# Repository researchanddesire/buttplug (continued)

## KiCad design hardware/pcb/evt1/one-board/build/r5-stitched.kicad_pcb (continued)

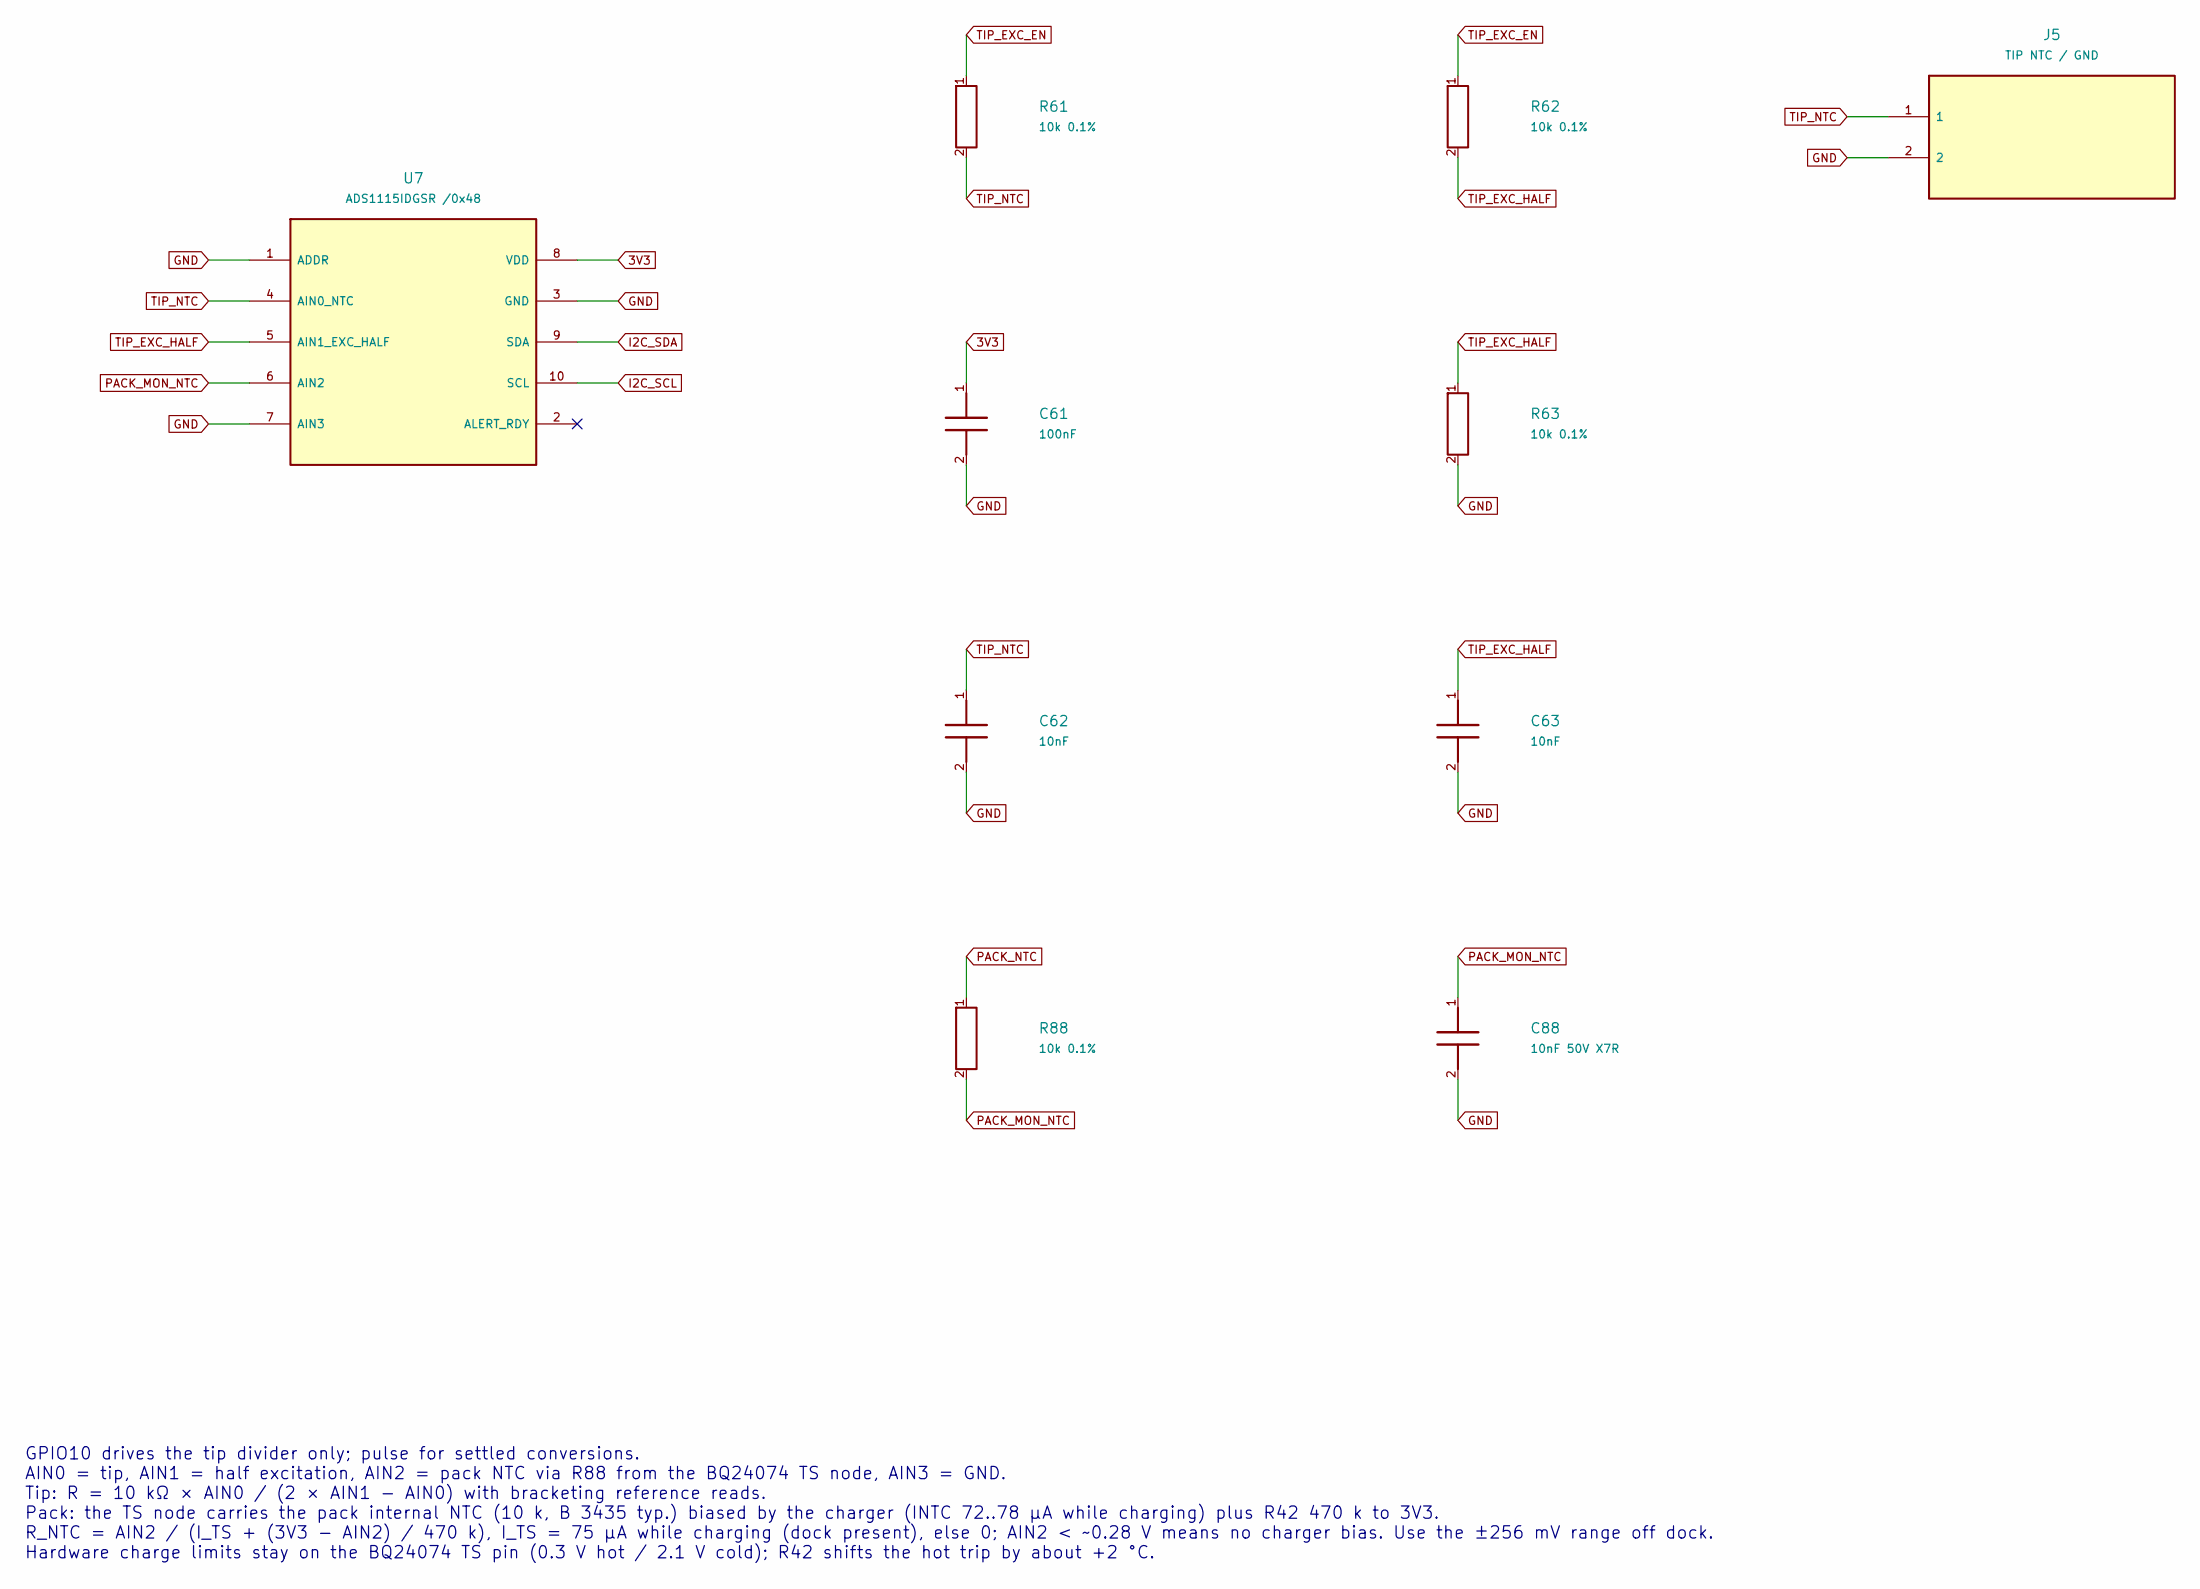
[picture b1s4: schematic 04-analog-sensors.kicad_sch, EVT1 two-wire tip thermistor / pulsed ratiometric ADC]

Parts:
C61: 100nF; C_0402_1005Metric
C62, C63: 10nF; C_0402_1005Metric
C88: 10nF 50V X7R; C_0402_1005Metric; Manufacturer Part Number GRM155R71H103KA88D
J5: TIP NTC / GND; JST_SH_SM02B-SRSS-TB_1x02-1MP_P1.00mm_Horizontal; Manufacturer Part Number SM02B-SRSS-TB(LF)(SN); LCSC Part Number C160402
R61, R62, R63: 10k 0.1%; R_0402_1005Metric
R88: 10k 0.1%; R_0402_1005Metric; Manufacturer Part Number TNPW040210K0BEED
U7: ADS1115IDGSR /0x48; VSSOP-10_3x3mm_P0.5mm

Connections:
3V3: C61.1, U7.8 (VDD); also elsewhere on the board
GND: C61.2, C62.2, C63.2, C88.2, J5.2, R63.2, U7.1 (ADDR), U7.3 (GND), U7.7 (AIN3); also elsewhere on the board
I2C_SCL: U7.10 (SCL); also elsewhere on the board
I2C_SDA: U7.9 (SDA); also elsewhere on the board
PACK_MON_NTC: C88.1, R88.2, U7.6 (AIN2); also elsewhere on the board
TIP_EXC_HALF: C63.1, R62.2, R63.1, U7.5 (AIN1_EXC_HALF)
TIP_NTC: C62.1, J5.1, R61.2, U7.4 (AIN0_NTC)

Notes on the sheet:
GPIO10 drives the tip divider only; pulse for settled conversions. AIN0 = tip, AIN1 = half excitation, AIN2 = pack NTC via R88 from the BQ24074 TS node, AIN3 = GND. Tip: R = 10 kΩ × AIN0 / (2 × AIN1 − AIN0) with bracketing reference reads. Pack: the TS node carries the pack internal NTC (10 k, B 34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

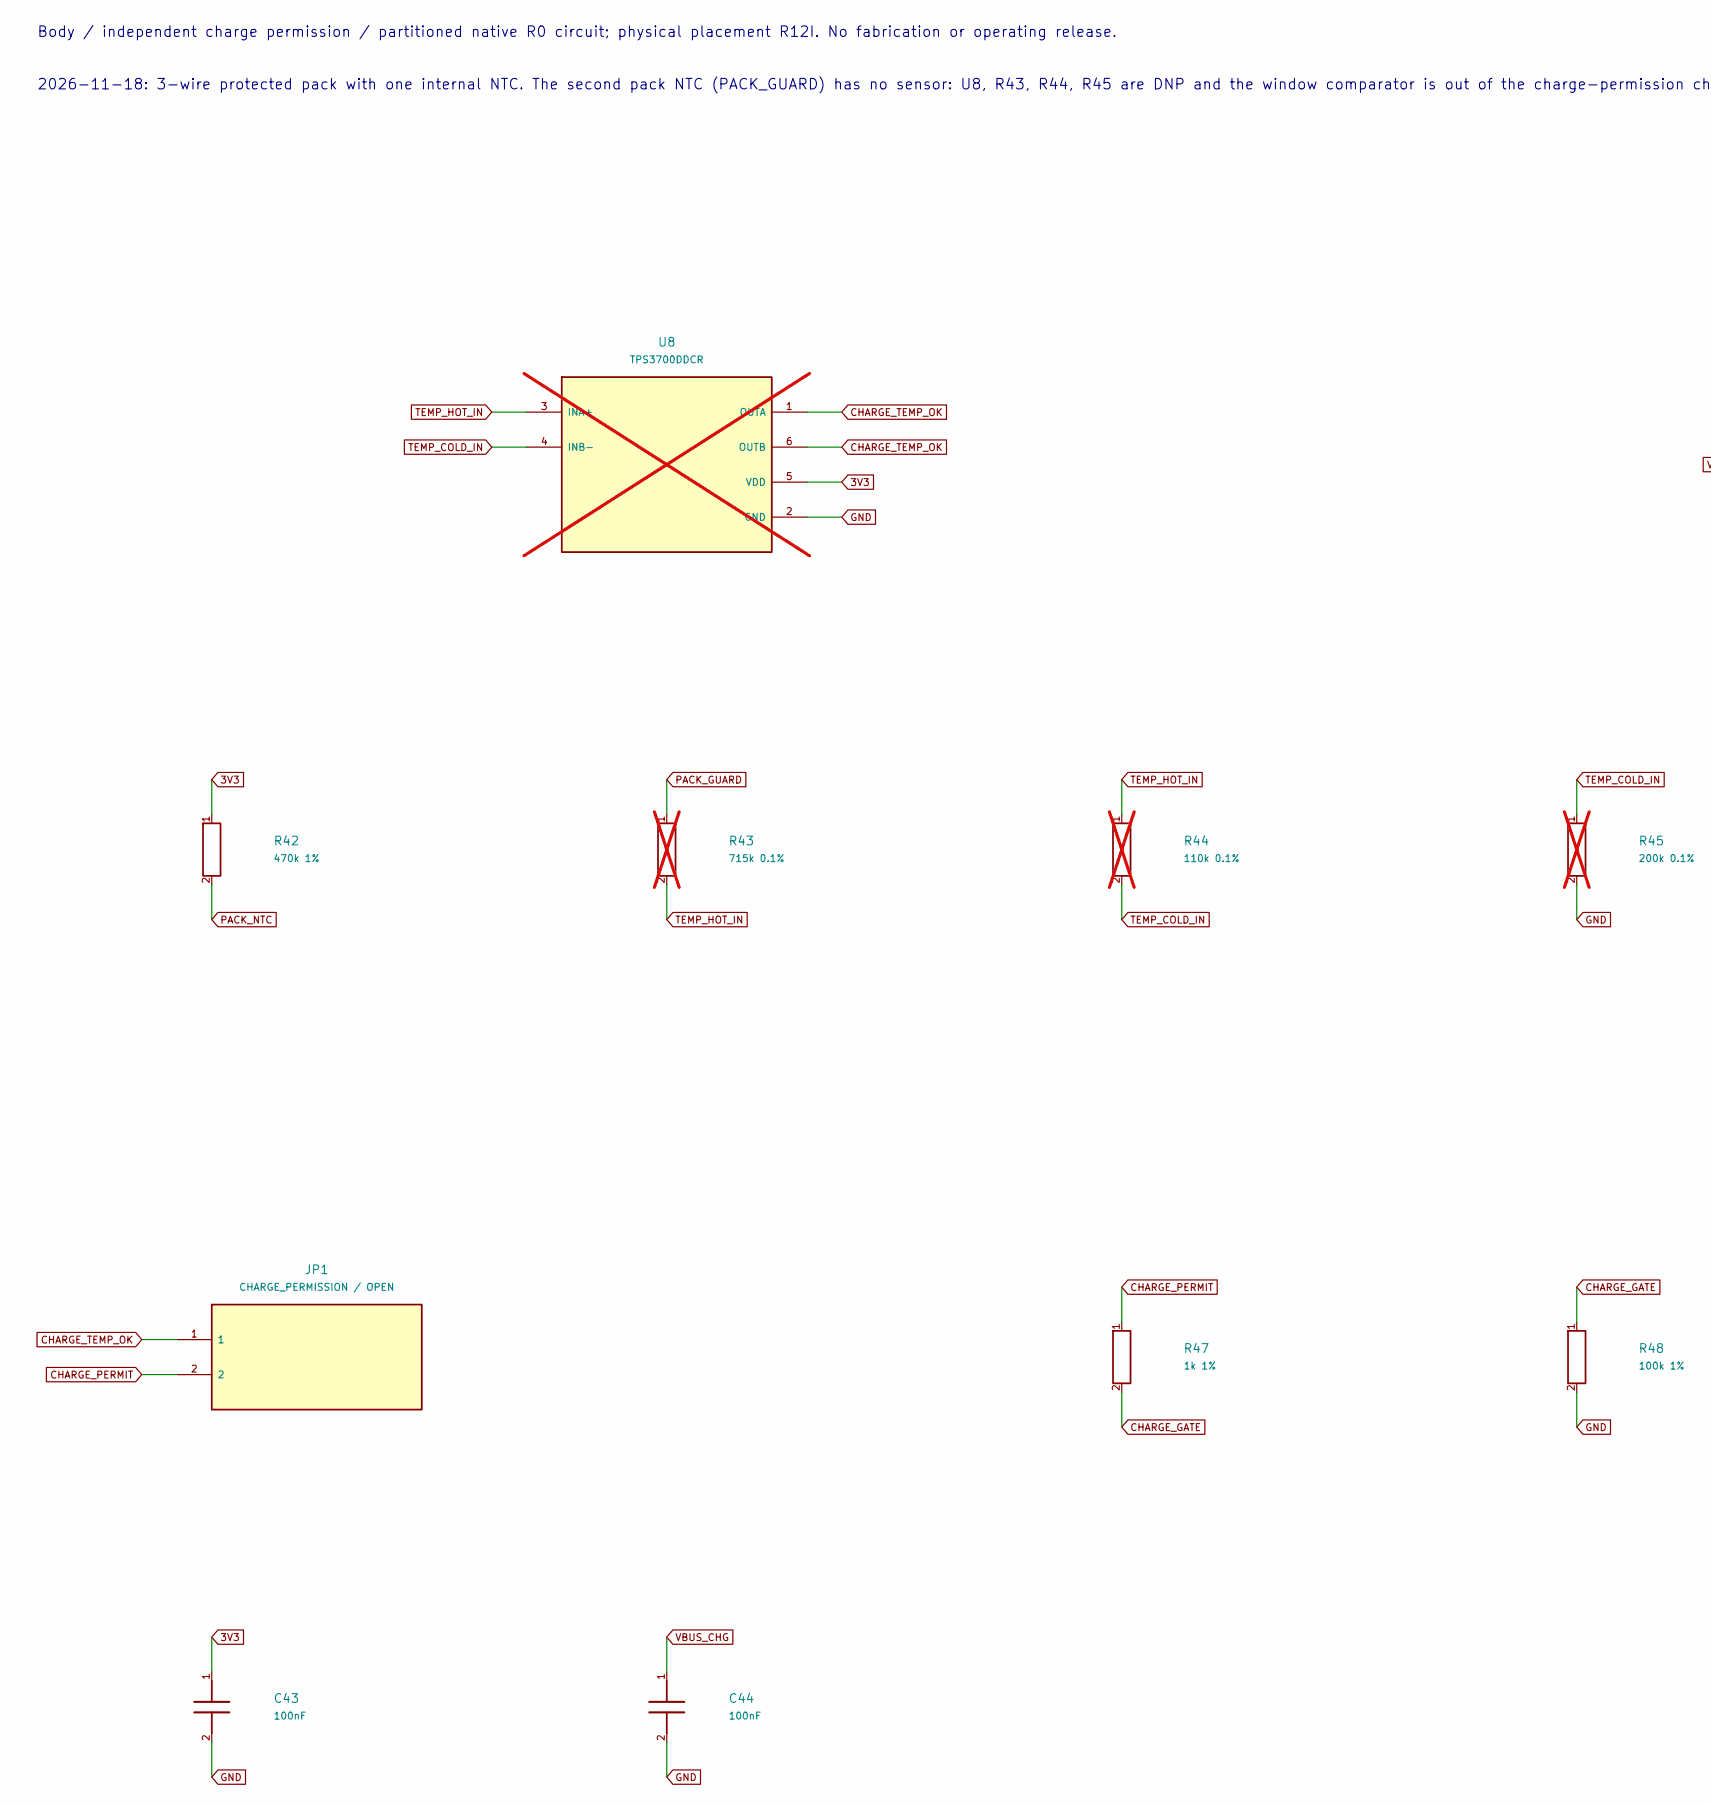
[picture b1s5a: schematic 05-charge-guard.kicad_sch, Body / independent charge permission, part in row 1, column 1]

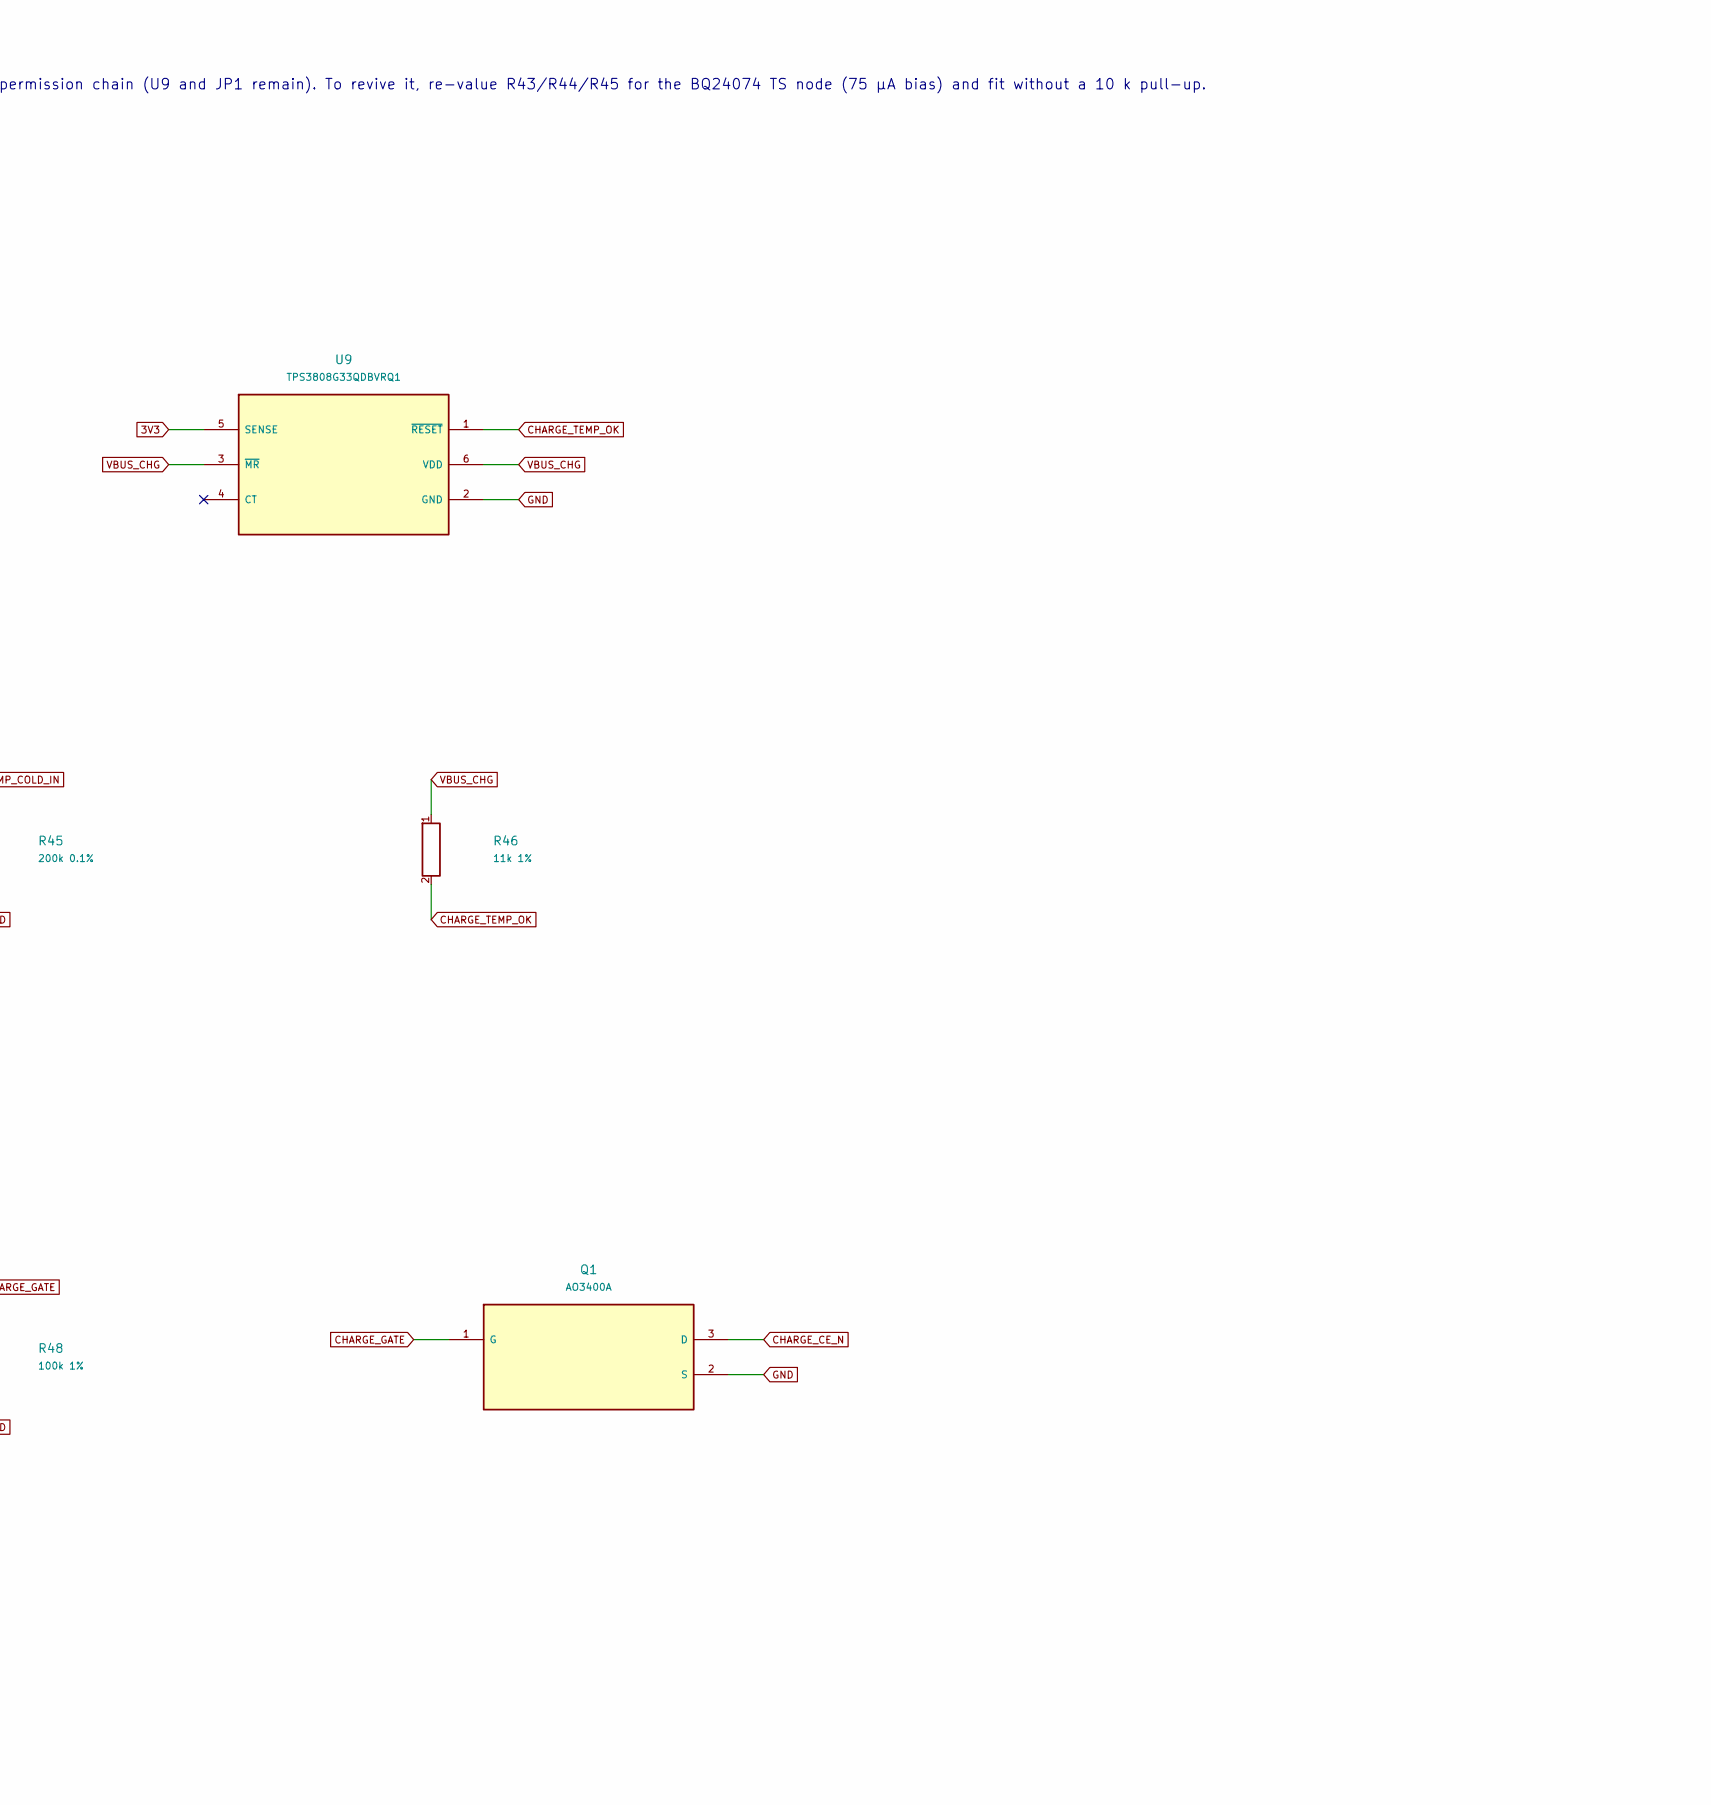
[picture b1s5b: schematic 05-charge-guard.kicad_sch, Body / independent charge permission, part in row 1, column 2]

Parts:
C43, C44: 100nF; Murata_GRM18_0603_Reflow
JP1: CHARGE_PERMISSION / OPEN; SolderJumper-2_P1.3mm_Open_RoundedPad1.0x1.5mm
Q1: AO3400A; SOT-23
R42: 470k 1%; R_0402_1005Metric; Manufacturer Part Number 0402WGF4703TCE
R43: 715k 0.1%; RESI_PTFR0805_C16003; Manufacturer Part Number PTFR0805B715KP9; LCSC Part Number C2849329; not fitted
R44: 110k 0.1%; Vishay_TNPW0603_IEC_Reflow; not fitted
R45: 200k 0.1%; Vishay_TNPW0603_IEC_Reflow; Manufacturer Part Number ERA3AEB204V; LCSC Part Number C473261; not fitted
R46: 11k 1%; R_0402_1005Metric; Manufacturer Part Number RT0402BRD0711KL; LCSC Part Number C705064
R47: 1k 1%; R_0402_1005Metric
R48: 100k 1%; R_0402_1005Metric
U8: TPS3700DDCR; TSOT-23-6; not fitted
U9: TPS3808G33QDBVRQ1; SOT-23-6; Manufacturer Part Number TPS3808G33QDBVRQ1; LCSC Part Number C414616

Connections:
3V3: C43.1, R42.1, U8.5 (VDD), U9.5 (SENSE); also elsewhere on the board
CHARGE_CE_N: Q1.3 (D); also elsewhere on the board
CHARGE_GATE: Q1.1 (G), R47.2, R48.1
CHARGE_PERMIT: JP1.2, R47.1
CHARGE_TEMP_OK: JP1.1, R46.2, U8.1 (OUTA), U8.6 (OUTB), U9.1 (~RESET)
GND: C43.2, C44.2, Q1.2 (S), R45.2, R48.2, U8.2 (GND), U9.2 (GND); also elsewhere on the board
TEMP_COLD_IN: R44.2, R45.1, U8.4 (INB-)
TEMP_HOT_IN: R43.2, R44.1, U8.3 (INA+)
VBUS_CHG: C44.1, R46.1, U9.3 (~MR), U9.6 (VDD); also elsewhere on the board

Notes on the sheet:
Body / independent charge permission / partitioned native R0 circuit; physical placement R12I. No fabrication or operating release.
2026-11-18: 3-wire protected pack with one internal NTC. The second pack NTC (PACK_GUARD) has no sensor: U8, R43, R44, R45 are DNP and the window comparator is out of the charge-permission chain (U9 and JP1 remain). To revive it, re-value R43/R44/R45 for the BQ24074 TS node (75 µA bias) and fit wit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

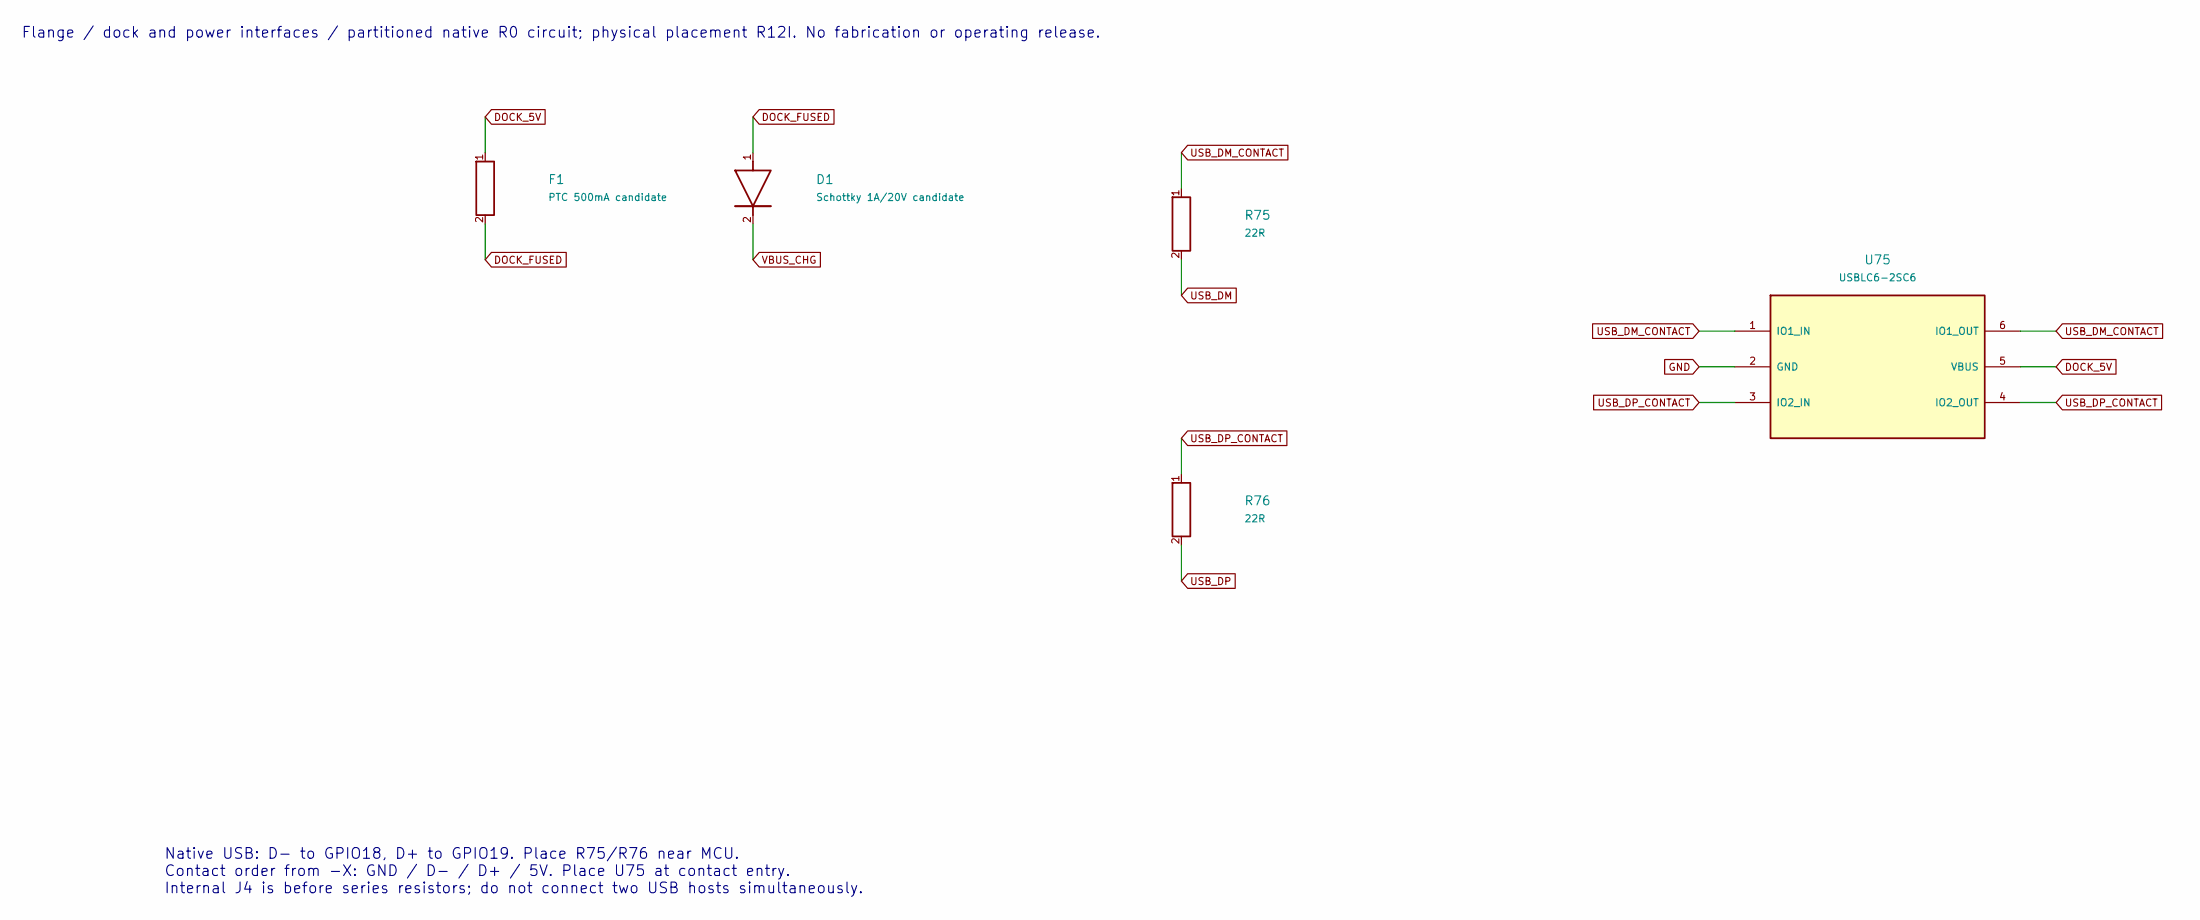
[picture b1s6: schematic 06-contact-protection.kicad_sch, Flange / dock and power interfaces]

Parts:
D1: Schottky 1A/20V candidate; Diodes_B140HW_SOD123_A1_K2
F1: PTC 500mA candidate; Fuse_1206_3216Metric
R75, R76: 22R; R_0402_1005Metric; Manufacturer Part Number RC0402FR-0722RL; LCSC Part Number C114765
U75: USBLC6-2SC6; SOT-23-6

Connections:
DOCK_5V: F1.1, U75.5 (VBUS); also elsewhere on the board
DOCK_FUSED: D1.1, F1.2
GND: U75.2 (GND); also elsewhere on the board
USB_DM: R75.2; also elsewhere on the board
USB_DM_CONTACT: R75.1, U75.1 (IO1_IN), U75.6 (IO1_OUT); also elsewhere on the board
USB_DP: R76.2; also elsewhere on the board
USB_DP_CONTACT: R76.1, U75.3 (IO2_IN), U75.4 (IO2_OUT); also elsewhere on the board
VBUS_CHG: D1.2; also elsewhere on the board

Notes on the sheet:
Flange / dock and power interfaces / partitioned native R0 circuit; physical placement R12I. No fabrication or operating release.
Native USB: D- to GPIO18, D+ to GPIO19. Place R75/R76 near MCU. Contact order from -X: GND / D- / D+ / 5V. Place U75 at contact entry. Internal J4 is before series resistors; do not connect two USB hosts simultaneously.

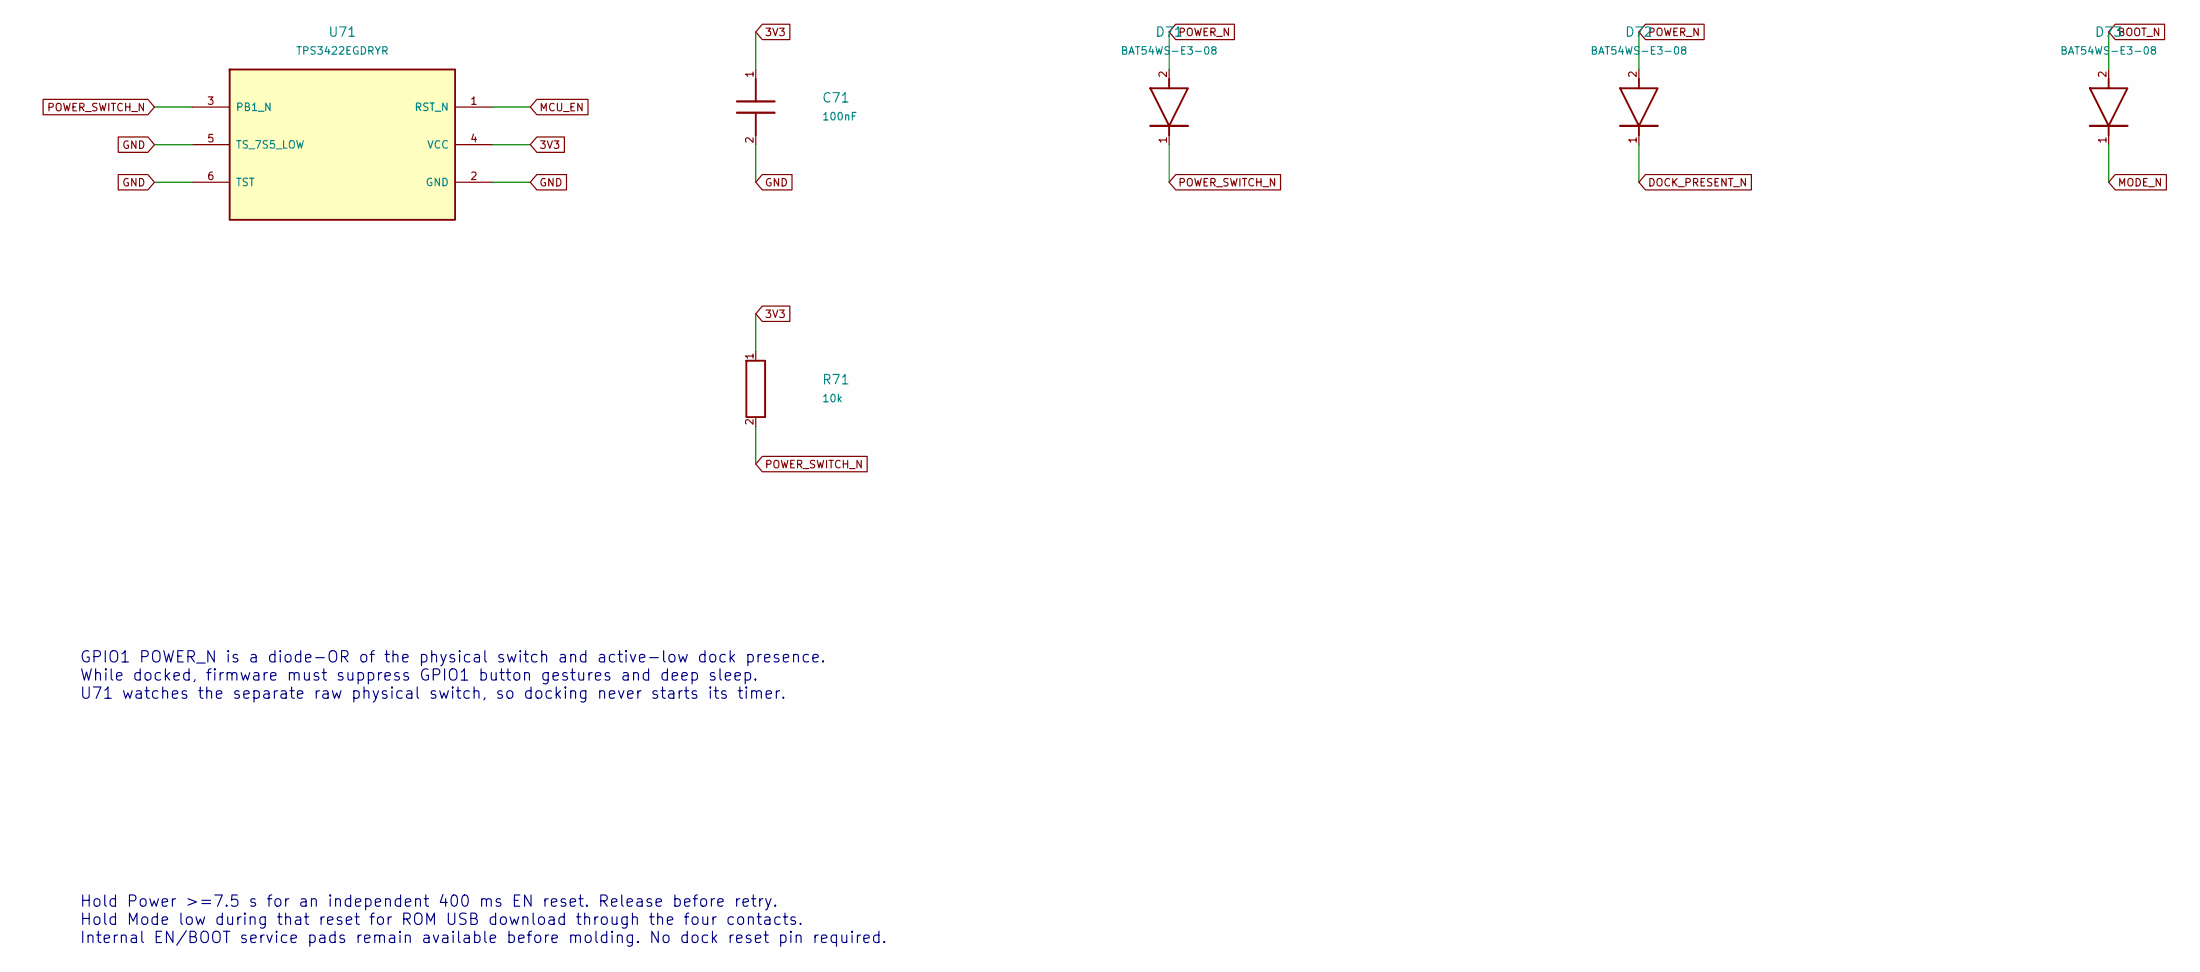
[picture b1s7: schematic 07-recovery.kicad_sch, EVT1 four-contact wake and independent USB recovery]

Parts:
C71: 100nF; C_0402_1005Metric
D71, D72, D73: BAT54WS-E3-08; D_SOD-323
R71: 10k; R_0402_1005Metric
U71: TPS3422EGDRYR; Texas_USON-6_1x1.45mm_P0.5mm_SMD

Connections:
3V3: C71.1, R71.1, U71.4 (VCC); also elsewhere on the board
BOOT_N: D73.2 (1); also elsewhere on the board
DOCK_PRESENT_N: D72.1 (2); also elsewhere on the board
GND: C71.2, U71.2 (GND), U71.5 (TS_7S5_LOW), U71.6 (TST); also elsewhere on the board
MCU_EN: U71.1 (RST_N); also elsewhere on the board
MODE_N: D73.1 (2); also elsewhere on the board
POWER_N: D71.2 (1), D72.2 (1); also elsewhere on the board
POWER_SWITCH_N: D71.1 (2), R71.2, U71.3 (PB1_N); also elsewhere on the board

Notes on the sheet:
GPIO1 POWER_N is a diode-OR of the physical switch and active-low dock presence. While docked, firmware must suppress GPIO1 button gestures and deep sleep. U71 watches the separate raw physical switch, so docking never starts its timer.
Hold Power >=7.5 s for an independent 400 ms EN reset. Release before retry. Hold Mode low during that reset for ROM USB download through the four contacts. Internal EN/BOOT service pads remain available before molding. No dock reset pin required.

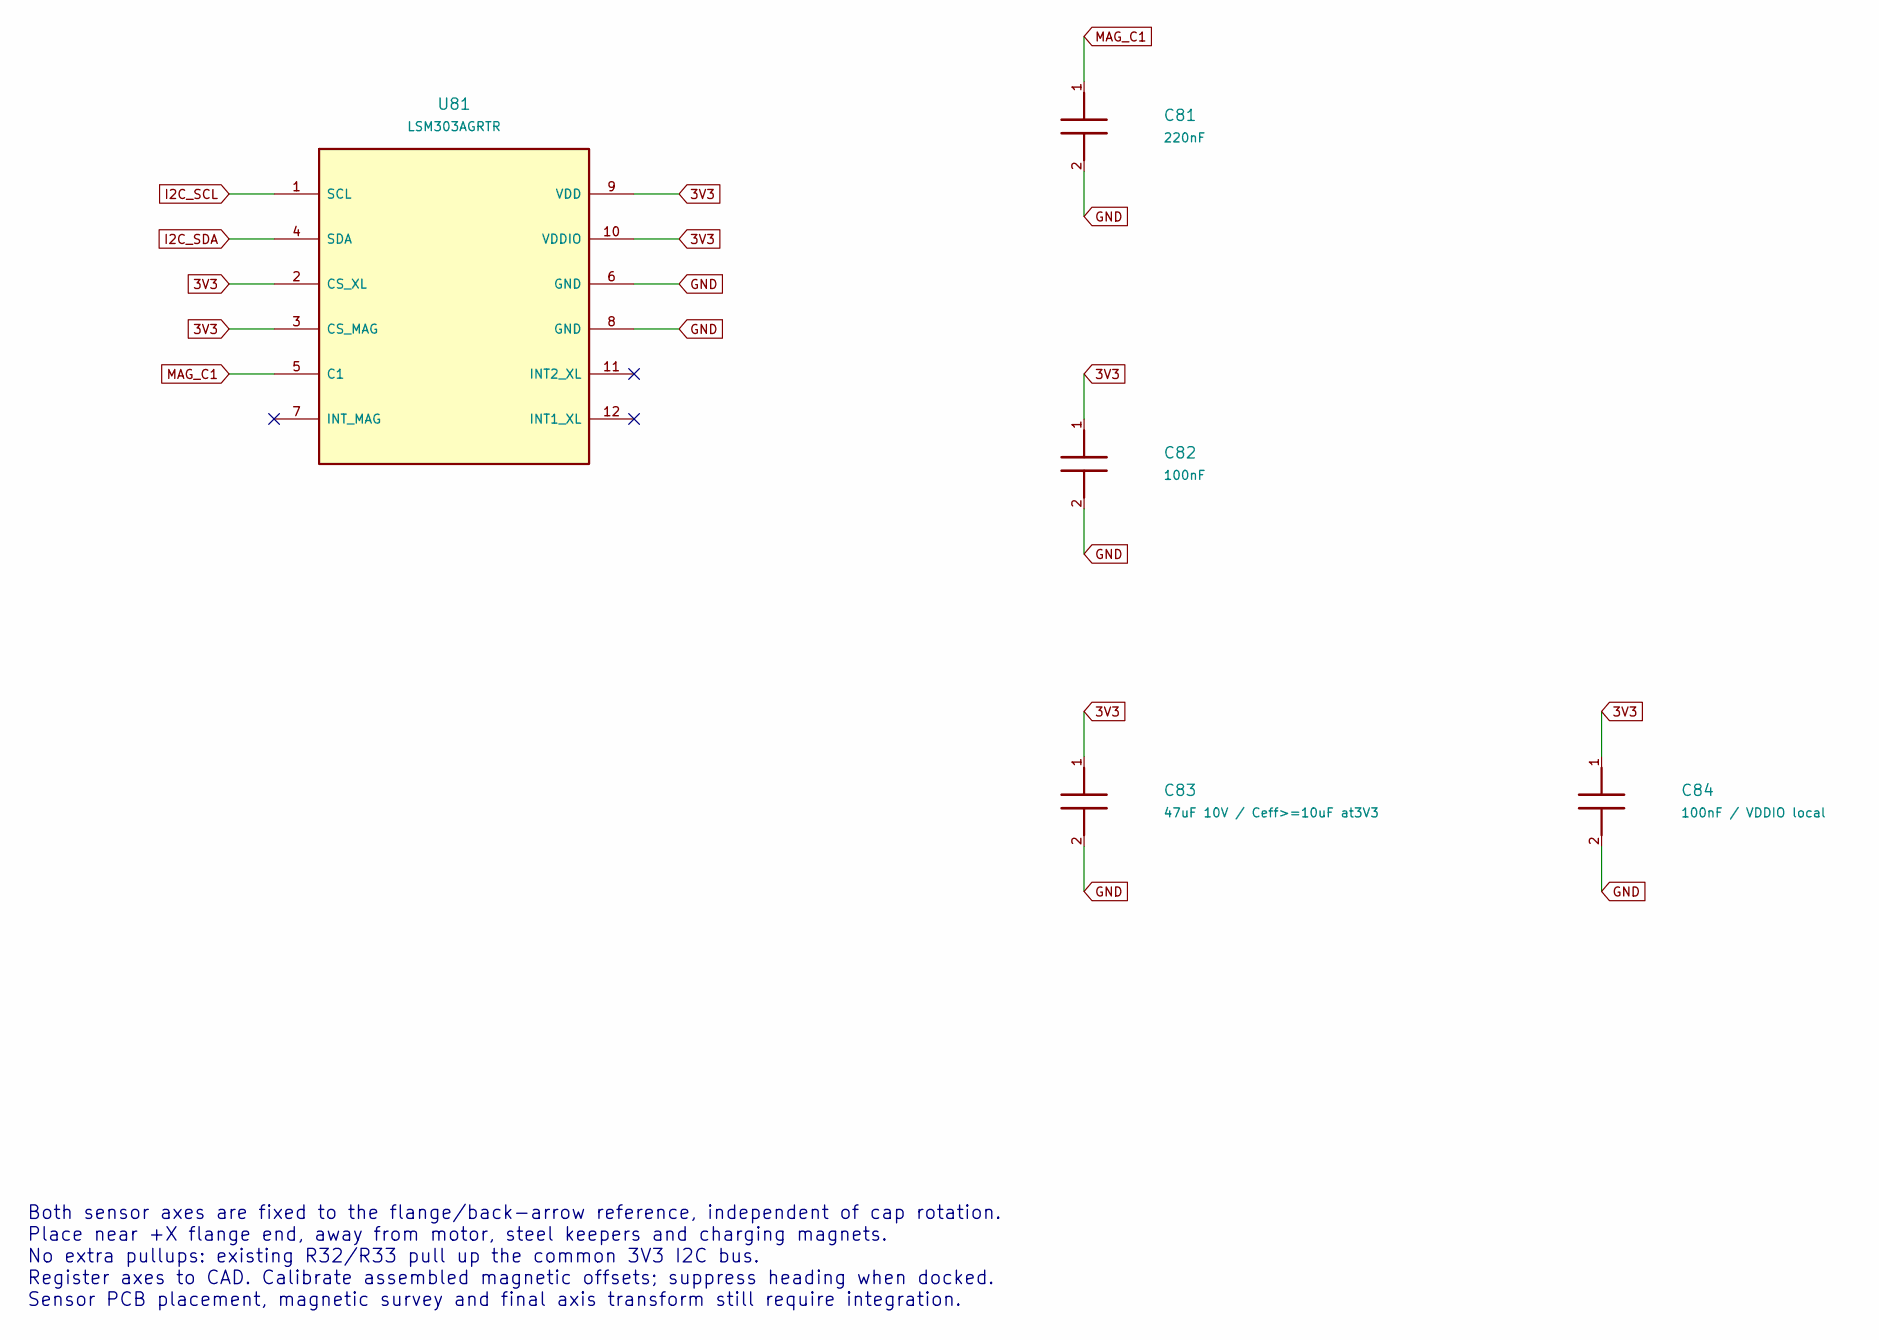
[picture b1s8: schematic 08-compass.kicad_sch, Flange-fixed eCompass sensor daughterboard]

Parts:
C81: 220nF; C_0402_1005Metric
C82: 100nF; C_0402_1005Metric
C83: 47uF 10V / Ceff>=10uF at3V3; C_0805_2012Metric; Manufacturer Part Number MSASL21GBB5476MTNA01; LCSC Part Number C386058
C84: 100nF / VDDIO local; C_0402_1005Metric
U81: LSM303AGRTR; LGA-12_2x2mm_P0.5mm

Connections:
3V3: C82.1, C83.1, C84.1, U81.2 (CS_XL), U81.3 (CS_MAG), U81.9 (VDD), U81.10 (VDDIO); also elsewhere on the board
GND: C81.2, C82.2, C83.2, C84.2, U81.6 (GND), U81.8 (GND); also elsewhere on the board
I2C_SCL: U81.1 (SCL); also elsewhere on the board
I2C_SDA: U81.4 (SDA); also elsewhere on the board
MAG_C1: C81.1, U81.5 (C1)

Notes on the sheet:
Both sensor axes are fixed to the flange/back-arrow reference, independent of cap rotation. Place near +X flange end, away from motor, steel keepers and charging magnets. No extra pullups: existing R32/R33 pull up the common 3V3 I2C bus. Register axes to CAD. Calibrate assembled magnetic offsets; s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

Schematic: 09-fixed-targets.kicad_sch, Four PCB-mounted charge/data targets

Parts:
CT1, CT2, CT3, CT4: 1946-0-00-15-00-00-03-0; MillMax_1946_0_PTH_Study

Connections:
DOCK_5V: CT4.1; also elsewhere on the board
GND: CT1.1; also elsewhere on the board
USB_DM_CONTACT: CT2.1; also elsewhere on the board
USB_DP_CONTACT: CT3.1; also elsewhere on the board

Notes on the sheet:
Same GND/D−/D+/5V order on6mm pitch. Fixed39-part placement is mechanically source-bound. Body electronics/J7 interface unchanged. No new output/driver flags are added.

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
